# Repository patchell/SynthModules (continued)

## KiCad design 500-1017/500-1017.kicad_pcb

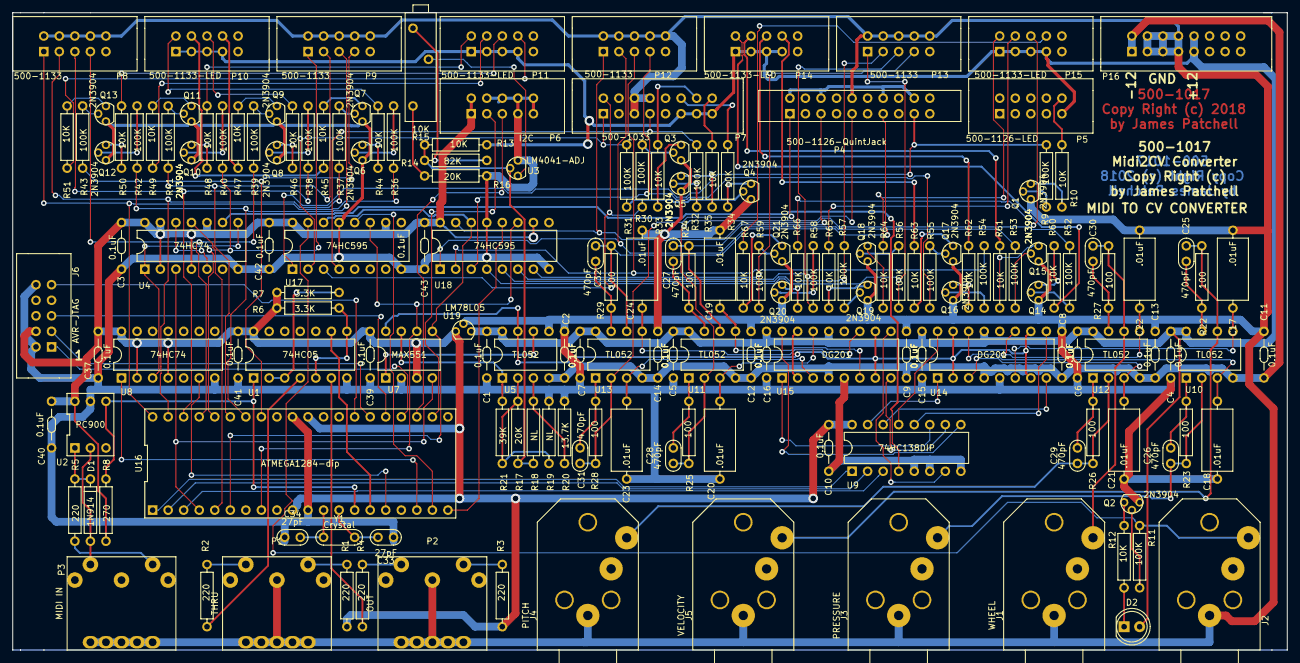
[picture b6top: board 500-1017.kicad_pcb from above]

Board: 2 copper layers, 208.3 x 104.1 mm, 171 parts (0 on the bottom side), 164 nets.

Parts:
C1, C2, C3, C4, C5, C6, C7, C8, C9, C10, C11, C12, C13, C14, C15, C16, C37, C39, C40, C41, C42, C43: 0.1uF; CAP-Bypass-0.3
C17, C18, C19, C20, C21, C22, C23, C24: .01uF; CAP-AXIAL-0.5x0.2
C25, C26, C27, C28, C29, C30, C31, C32: 470pF; CAP-0.1
C33, C34: 27pF; CAP-0.1
D1: 1N914; DIODE0.4
D2: LED_ALT; LED_5.0mm
J1: WHEEL; PHONE-SC112A
J2: GATE; PHONE-SC112A
J3: PRESSURE; PHONE-SC112A
J4: PITCH; PHONE-SC112A
J5: VELOCITY; PHONE-SC112A
J6: AVR-JTAG; IDC5x2_Vert
P1: THRU; DIN-5-PIN
P2: OUT; DIN-5-PIN
P3: MIDI IN; DIN-5-PIN
P4: 500-1126-QuintJack; IDC10x2-Vert
P5: 500-1126-LED; IDC5x2_Vert
P6: I2C; IDC5x2_Vert
P7: 500-1033; IDC8x2_Vert
P8, P9, P12, P13: 500-1133; IDC5x2_Vert
P10, P11, P14, P15: 500-1133-LED; IDC5x2_Vert
P16: EurorackPower16pin; IDC8x2_Vert
Q1, Q2, Q3, Q4, Q5, Q6, Q7, Q8, Q9, Q10, Q11, Q12, Q13, Q14, Q15, Q16, Q17, Q18, Q19, Q20, Q21: 2N3904; TO92
R1, R2, R3, R4, R5: 220; AXIAL0.4
R6, R7: 3.3K; AXIAL0.4
R8: 270; AXIAL0.4
R9, R11, R30, R31, R32, R36, R37, R38, R39, R40, R41, R42, R43, R52, R53, R54, R55, R56, R57, R58, R59: 100K; AXIAL0.4
R10, R12, R13, R33, R34, R35, R44, R45, R46, R47, R48, R49, R50, R51, R60, R61, R62, R63, R64, R65, R66, R67: 10K; AXIAL0.4
R14: 82K; AXIAL0.4
R15: 10K; Trimpot-3006
R16, R17: 20K; AXIAL0.4
R18, R19: NL; AXIAL0.4
R20: 13.7K; AXIAL0.4
R21: 39K; AXIAL0.4
R22, R23, R24, R25, R26, R27, R28, R29: 100; AXIAL0.4
U1: 74HC05; DIP-14.3
U2: PC900; DIP-6.3
U3: LM4041-ADJ; TO92
U4, U8: 74HC74; DIP-14.3
U5, U10, U11, U12, U13: TL052; DIP8.3
U7: MAX551; DIP8.3
U9: 74HC138DIP; DIP-16.3
U14, U15: DG201; DIP-16.3
U16: ATMEGA1284-dip; DIP-40.6
U17, U18: 74HC595; DIP-16.3
U19: LM78L05; TO92
Y1: Crystal; XTAL

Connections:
+15V0: C1.1, C4.1, C5.1, C6.1, C7.1, C15.1, C16.1, D2.2, P5.9, P7.11, P7.13, P7.15, P10.1, P10.3, P10.5, P10.7, P11.1, P11.3, P11.5, P11.7, P14.1, P14.3, P14.5, P14.7, P15.1, P15.3, P15.5, P15.7, P16.9, P16.10, R13.1, U5.8, U10.8, U11.8, U12.8, U13.8, U14.13, U15.13, U19.3
-15V0: C2.1, C8.1, C9.1, C11.1, C12.1, C13.1, C14.1, P16.1, P16.2, U5.4, U10.4, U11.4, U12.4, U13.4, U14.4, U15.4
/BEND1: C30.2, J1.3, R27.2, U12.6
/BEND2: C32.2, P4.13, R29.2, U13.6
/CPU/CLR_IRQ: U8.1, U16.18
/CPU/DACCLK: U4.11, U16.5
/CPU/DACDONE: U8.6, U16.16
/CPU/DACSEL0: U9.1, U16.1
/CPU/DACSEL1: U9.2, U16.2
/CPU/DACSEL2: U9.3, U16.3
/CPU/LD_DAC: U4.3, U7.4, U16.4
/CPU/LD_GATES: U16.19, U17.12
/CPU/LD_TRIGS: U16.20, U18.12
/CPU/MIDI_IN: R8.2, U1.1, U2.4, U16.14
/CPU/MIDI_OUT: U1.9, U16.15
/CPU/SCL: P6.3, U16.22
/CPU/SDA: P6.5, U16.23
/CPU/SPICLK: U7.6, U16.8, U17.11, U18.11
/CPU/SPIDATA: U7.5, U16.6, U17.14, U18.14
/CPU/TCK: J6.1, U16.24
/CPU/TDI: J6.9, U16.27
/CPU/TDO: J6.3, U16.26
/CPU/TMS: J6.5, U16.25
/CPU/TRIG0: P8.1, R36.1, U16.40
/CPU/TRIG1: P8.3, R37.1, U16.39
/CPU/TRIG2: P8.5, R38.1, U16.38
/CPU/TRIG3: P8.7, R39.1, U16.37
/CPU/TRIG4: P9.1, R40.1, U16.36
/CPU/TRIG5: P9.3, R41.1, U16.35
/CPU/TRIG6: P9.5, R42.1, U16.34
/CPU/TRIG7: P9.7, R43.1, U16.33
/CPU/TRIG8: P12.1, R52.1, U18.15
/CPU/TRIG9: P12.3, R53.1, U18.1
/CPU/TRIG10: P12.5, R54.1, U18.2
/CPU/TRIG11: P12.7, R55.1, U18.3
/CPU/TRIG12: P13.1, R56.1, U18.4
/CPU/TRIG13: P13.3, R57.1, U18.5
/CPU/TRIG14: P13.5, R58.1, U18.6
/CPU/TRIG15: P13.7, R59.1, U18.7
/GATE0: J2.3, R11.1, U17.15
/GATE1: P4.17, R9.1, U17.1
/GATE2: P7.1, R31.2, U17.2
/GATE3: P7.2, R30.2, U17.3
/GATE4: P7.7, R32.2, U17.4
/MIDI_CLOCK: P7.12, R34.2
/MIDI_RESET: P7.16, R35.2
/PITCH1: C29.2, J4.3, R26.2, U12.2
/PITCH2: C31.2, P4.1, R28.2, U13.2
/PRES1: C26.2, J3.3, R23.2, U10.2
/PRES2: C28.2, P4.9, R25.2, U11.2
/SPI DAC/DacOut: U5.7, U7.8, U14.2, U14.7, U14.10, U14.15, U15.2, U15.7, U15.10, U15.15
/SPI DAC/SHgate: U4.9, U9.4
/STARTSTOP: P7.14, R33.2
/VELO1: C25.2, J5.3, R22.2, U10.6
/VELO2: C27.2, P4.5, R24.2, U11.6
GND: C1.2, C2.2, C3.2, C4.2, C5.2, C6.2, C7.2, C8.2, C9.2, C10.2, C11.2, C12.2, C13.2, C14.2, C15.2, C16.2, C17.2, C18.2, C19.2, C20.2, C21.2, C22.2, C23.2, C24.2, C33.2, C34.2, C37.2, C39.2, C40.2, C41.2, C42.2, C43.2, J1.1, J2.1, J3.1, J4.1, J5.1, J6.2, J6.10, P1.2, P1.6, P1.7, P1.8, P1.9, P1.10, P2.2, P2.6, P2.7, P2.8, P2.9, P2.10, P3.6, P3.7, P3.8, P3.9, P3.10, P4.2, P4.6, P4.10, P4.14, P4.18, P6.4, P6.6, P6.7, P6.8, P6.9, P6.10, P7.5, P7.6, P7.8, P8.2, P8.4, P8.6, P8.8, P8.10, P9.2, P9.4, P9.6, P9.8, P9.10, P12.2, P12.4, P12.6, P12.8, P12.10, P13.2, P13.4, P13.6, P13.8, P13.10, P16.3, P16.4, P16.5, P16.6, P16.7, P16.8, Q1.1, Q2.1, Q3.1, Q4.1, Q5.1, Q6.1, Q7.1, Q8.1, Q9.1, Q10.1, Q11.1, Q12.1, Q13.1, Q14.1, Q15.1, Q16.1, Q17.1, Q18.1, Q19.1, Q20.1, Q21.1, R16.2, R19.2, R20.2, U1.7, U2.5, U3.3, U4.7, U5.5, U7.2, U8.7, U9.5, U9.6, U9.8, U14.5, U15.5, U16.11, U16.31, U17.8, U17.13, U18.8, U18.13, U19.2
unnamed: C17.1, U10.5, U14.6
unnamed: C18.1, U10.3, U14.14
unnamed: C19.1, U11.5, U15.6
unnamed: C20.1, U11.3, U15.14
unnamed: C21.1, U12.3, U14.3
unnamed: C22.1, U12.5, U14.11
unnamed: C23.1, U13.3, U15.3
unnamed: C24.1, U13.5, U15.11
unnamed: C25.1, R22.1, U10.7
unnamed: C26.1, R23.1, U10.1
unnamed: C27.1, R24.1, U11.7
unnamed: C28.1, R25.1, U11.1
unnamed: C29.1, R26.1, U12.1
unnamed: C30.1, R27.1, U12.7
unnamed: C31.1, R28.1, U13.1
unnamed: C32.1, R29.1, U13.7
unnamed: C33.1, U16.13, Y1.1
unnamed: C34.1, U16.12, Y1.2
unnamed: D1.1, R5.2, U2.1
unnamed: D1.2, P3.5, U2.2
unnamed: D2.1, R12.2
unnamed: P1.4, R1.1
unnamed: P1.5, R2.1
unnamed: P2.4, R3.1
unnamed: P2.5, R4.1
unnamed: P3.4, R5.1
unnamed: P5.10, R10.2
unnamed: P10.2, R44.2
unnamed: P10.4, R45.2
unnamed: P10.6, R46.2
unnamed: P10.8, R47.2
unnamed: P11.2, R48.2
unnamed: P11.4, R49.2
unnamed: P11.6, R50.2
unnamed: P11.8, R51.2
unnamed: P14.2, R60.2
unnamed: P14.4, R61.2
unnamed: P14.6, R62.2
unnamed: P14.8, R63.2
unnamed: P15.2, R64.2
unnamed: P15.4, R65.2
unnamed: P15.6, R66.2
unnamed: P15.8, R67.2
unnamed: Q1.2, R9.2
unnamed: Q1.3, R10.1
unnamed: Q2.2, R11.2
unnamed: Q2.3, R12.1
unnamed: Q3.2, R30.1
unnamed: Q3.3, R33.1
unnamed: Q4.2, R31.1
unnamed: Q4.3, R34.1
unnamed: Q5.2, R32.1
unnamed: Q5.3, R35.1
unnamed: Q6.2, R36.2
unnamed: Q6.3, R44.1
unnamed: Q7.2, R37.2
unnamed: Q7.3, R45.1
unnamed: Q8.2, R38.2
unnamed: Q8.3, R46.1
unnamed: Q9.2, R39.2
unnamed: Q9.3, R47.1
unnamed: Q10.2, R40.2
unnamed: Q10.3, R48.1
unnamed: Q11.2, R41.2
unnamed: Q11.3, R49.1
unnamed: Q12.2, R42.2
unnamed: Q12.3, R50.1
unnamed: Q13.2, R43.2
unnamed: Q13.3, R51.1
unnamed: Q14.2, R52.2
unnamed: Q14.3, R60.1
unnamed: Q15.2, R53.2
unnamed: Q15.3, R61.1
unnamed: Q16.2, R54.2
unnamed: Q16.3, R62.1
unnamed: Q17.2, R55.2
unnamed: Q17.3, R63.1
unnamed: Q18.2, R56.2
unnamed: Q18.3, R64.1
unnamed: Q19.2, R57.2
unnamed: Q19.3, R65.1
unnamed: Q20.2, R58.2
unnamed: Q20.3, R66.1
unnamed: Q21.2, R59.2
unnamed: Q21.3, R67.1
unnamed: R2.2, U1.4
unnamed: R4.2, U1.6
unnamed: R6.2, U1.5, U1.8
unnamed: R7.2, U1.2, U1.3
unnamed: R13.2, R14.1, R17.1, R18.1, U3.2
unnamed: R14.2, R15.1
unnamed: R15.2, U3.1
unnamed: R15.3, R16.1
unnamed: R17.2, R19.1, R21.1, U5.2
unnamed: R18.2, R20.1, U5.3
unnamed: R21.2, U5.1, U7.7
unnamed: U4.1, U4.8, U8.3
unnamed: U4.5, U4.12
unnamed: U5.6, U7.1
unnamed: U9.15, U14.1
unnamed: U9.14, U14.8
unnamed: U9.12, U14.9
unnamed: U9.13, U14.16
unnamed: U9.11, U15.1
unnamed: U9.10, U15.8
unnamed: U9.7, U15.9
unnamed: U9.9, U15.16
VCC: C3.1, C10.1, C37.1, C39.1, C40.1, C41.1, C42.1, C43.1, J6.4, P6.1, P6.2, R1.2, R3.2, R6.1, R7.1, R8.1, U1.14, U2.6, U4.2, U4.4, U4.10, U4.13, U4.14, U7.3, U8.2, U8.4, U8.14, U9.16, U16.10, U16.30, U17.10, U17.16, U18.10, U18.16, U19.1

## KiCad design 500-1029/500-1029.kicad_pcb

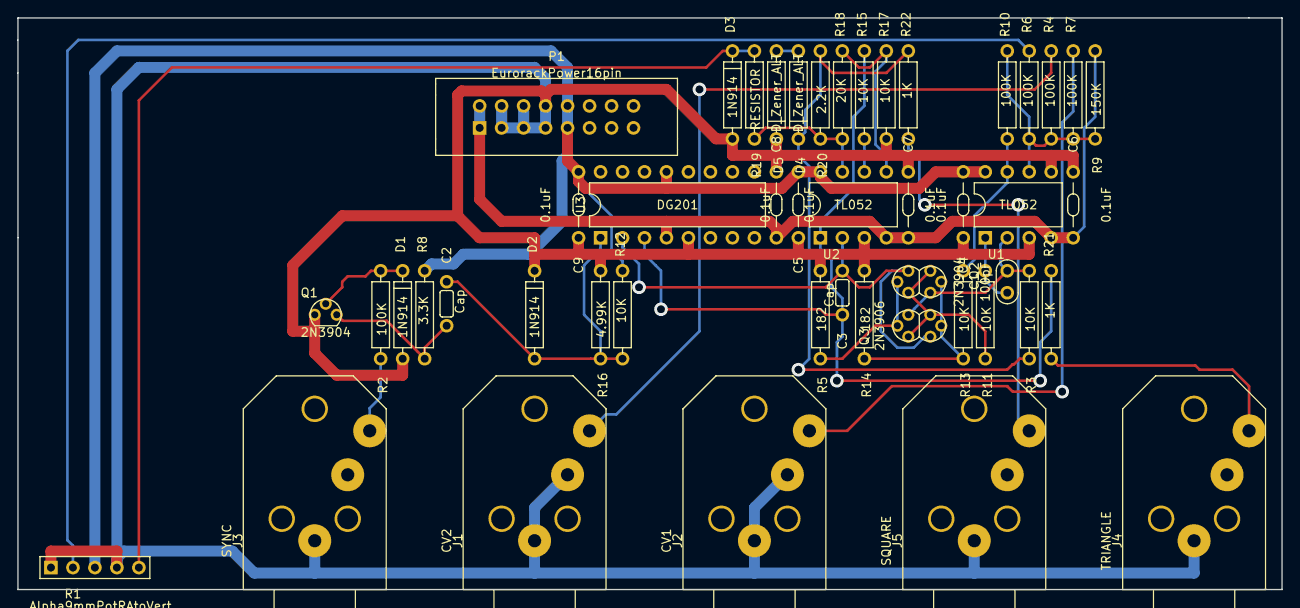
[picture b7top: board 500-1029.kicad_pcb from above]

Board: 2 copper layers, 146.0 x 66.0 mm, 48 parts (0 on the bottom side), 27 nets.

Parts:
C1: 100pF; CAP-0.1
C2, C3: Cap; CAP-GREENIE-0.2
C4, C5, C6, C7, C8, C9: 0.1uF; CAP-Bypass-0.3
D1, D2, D3: 1N914; DIODE0.4
D4, D5: D_Zener_ALT; DIODE0.4
J1: CV2; PHONE-SC112A
J2: CV1; PHONE-SC112A
J3: SYNC; PHONE-SC112A
J4: TRIANGLE; PHONE-SC112A
J5: SQUARE; PHONE-SC112A
P1: EurorackPower16pin; IDC8x2_Vert
Q1: 2N3904; TO92
Q2: 2N3904; DUAL_TO92
Q3: 2N3906; DUAL_TO92
R1: Alpha9mmPotRAtoVert; IDC5X1
R2, R4, R6, R7, R10: 100K; AXIAL0.4
R3, R11, R12, R13, R15, R17: 10K; AXIAL0.4
R5, R14: 182; AXIAL0.4
R8: 3.3K; AXIAL0.4
R9: 150K; AXIAL0.4
R16: 4.99K; AXIAL0.4
R18: 20K; AXIAL0.4
R19: RESISTOR; AXIAL0.4
R20: 2.2K; AXIAL0.4
R21, R22: 1K; AXIAL0.4
U1, U2: TL052; DIP8.3
U3: DG201; DIP-16.3

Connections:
+15V0: C4.1, C5.1, C9.1, P1.9, P1.10, R1.3, R8.1, R12.1, U1.8, U2.8, U3.13
-15V0: C6.1, C7.1, C8.1, P1.1, P1.2, R9.2, U1.4, U2.4, U3.4
GND: C4.2, C5.2, C6.2, C7.2, C8.2, C9.2, D1.2, D2.1, D3.2, D5.1, J1.1, J1.2, J2.1, J2.2, J3.1, J4.1, J5.1, P1.3, P1.4, P1.5, P1.6, P1.7, P1.8, Q1.1, R1.1, R1.4, R5.2, R14.2, R16.2, R17.2, U1.3, U1.5, U2.3, U3.5
unnamed: C1.1, Q2.3, Q3.3, R3.2, U1.2
unnamed: C1.2, R11.2, U1.1
unnamed: C2.1, Q1.3, R8.2
unnamed: C2.2, D2.2, R12.2, R16.1, U3.1
unnamed: C3.1, Q2.6, Q3.6, U2.2, U3.2
unnamed: C3.2, R15.1, R21.1, U2.1, U3.3
unnamed: D1.1, Q1.2, R2.2
unnamed: D3.1, R1.5, R19.2
unnamed: D4.1, R3.1, R20.2, R22.1
unnamed: D4.2, D5.2
unnamed: J1.3, R4.1
unnamed: J2.3, R7.1
unnamed: J3.3, R2.1
unnamed: J4.3, R21.2
unnamed: J5.3, R22.2
unnamed: Q2.1, Q2.4, Q3.1, Q3.4, R11.1
unnamed: Q2.2, Q3.5, R13.1, R14.1
unnamed: Q2.5, Q3.2, R5.1
unnamed: R1.2, R6.1
unnamed: R4.2, R6.2, R7.2, R9.1, R10.1, U1.6
unnamed: R10.2, R13.2, U1.7
unnamed: R15.2, U2.6
unnamed: R17.1, R18.1, U2.5
unnamed: R18.2, R19.1, R20.1, U2.7

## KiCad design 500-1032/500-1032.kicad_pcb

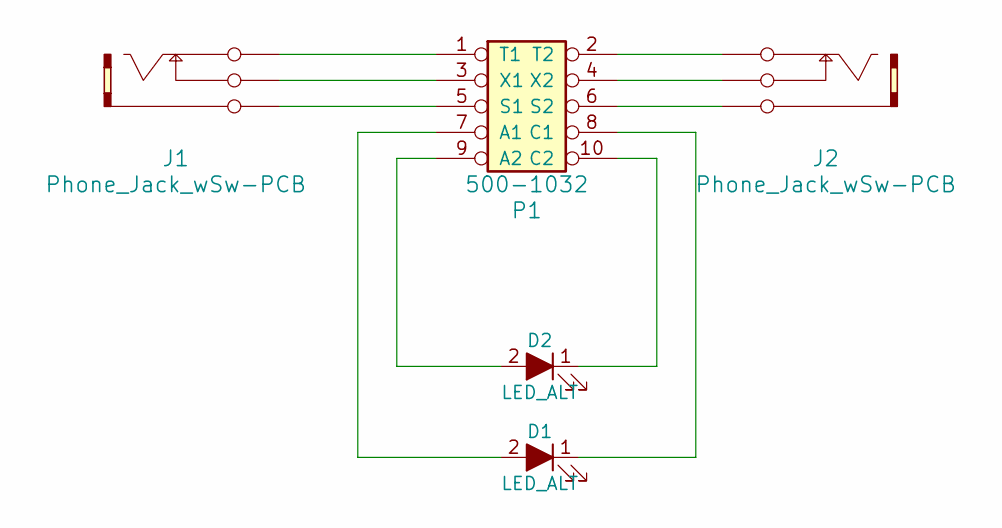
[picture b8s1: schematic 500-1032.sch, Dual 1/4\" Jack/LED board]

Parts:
D1, D2: LED_ALT; LED_D5.0mm
J1, J2: Phone_Jack_wSw-PCB; PHONE-SC112A
P1: 500-1032; IDC5x2_Vert

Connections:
unnamed: D1.1 (K), P1.8 (C1)
unnamed: D1.2 (A), P1.7 (A1)
unnamed: D2.1 (K), P1.10 (C2)
unnamed: D2.2 (A), P1.9 (A2)
unnamed: J1.1 (Gnd), P1.5 (S1)
unnamed: J1.2 (Sw), P1.3 (X1)
unnamed: J1.3 (Tip), P1.1 (T1)
unnamed: J2.1 (Gnd), P1.6 (S2)
unnamed: J2.2 (Sw), P1.4 (X2)
unnamed: J2.3 (Tip), P1.2 (T2)

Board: 2 copper layers, 5 parts (0 on the bottom side), 10 nets, no tracks yet.
